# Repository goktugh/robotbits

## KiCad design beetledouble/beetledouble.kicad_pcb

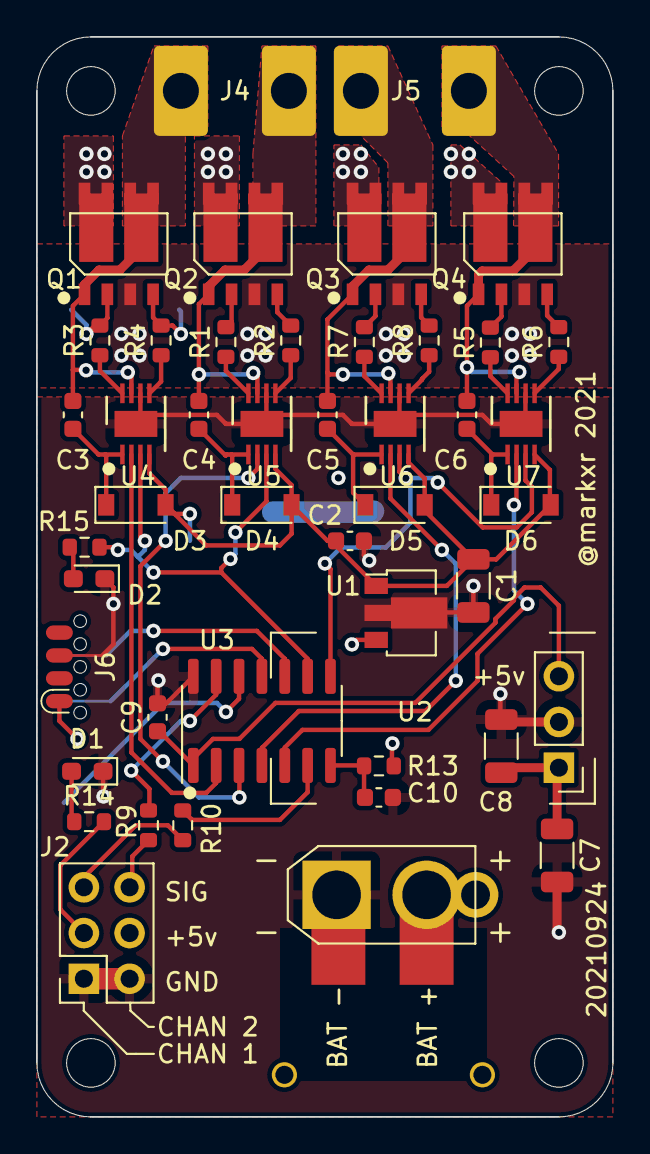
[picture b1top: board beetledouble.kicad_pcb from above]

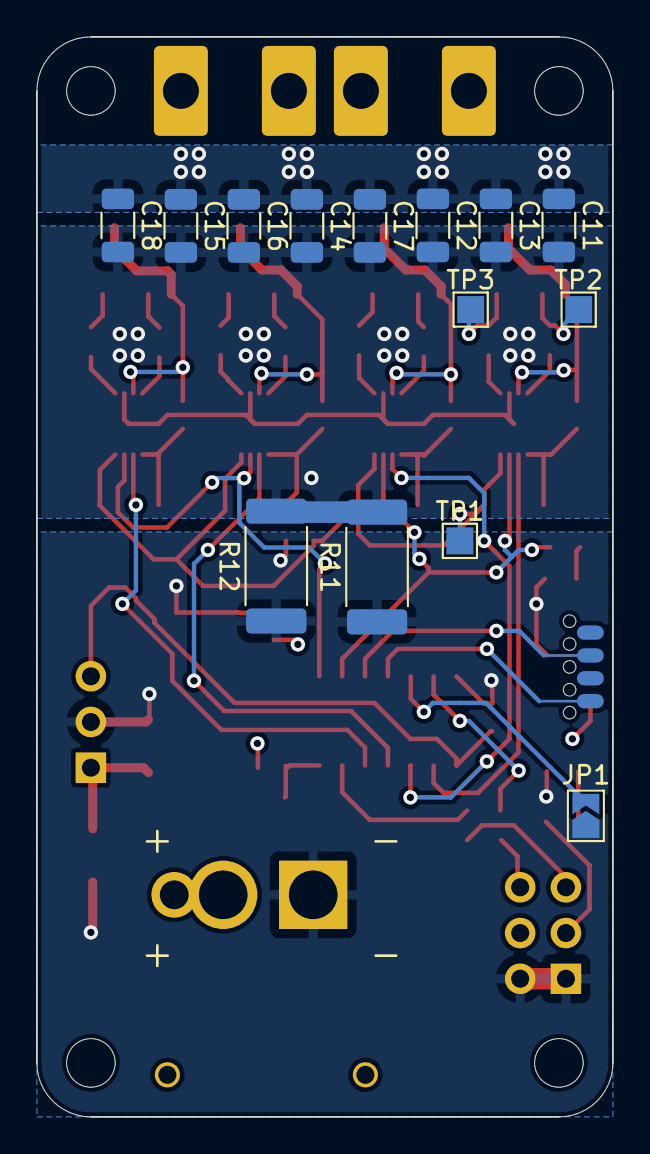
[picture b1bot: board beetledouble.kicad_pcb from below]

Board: 4 copper layers, 32.0 x 60.0 mm, 63 parts (14 on the bottom side), 45 nets.

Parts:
C1, C7, C8, C11, C12, C14, C15: 10uF 50V; C_1206_3216Metric
C2, C3, C4, C5, C6, C10: 2.2uF 50V; C_0603_1608Metric
C9: 0.1uF; C_0603_1608Metric
C13, C16, C17, C18: DNP; C_1206_3216Metric
D1, D2: LED; LED_0603_1608Metric_Pad1.05x0.95mm_HandSolder
D3, D4, D5, D6: B5819W; D_SOD-123
H1, H2, H3, H4: MountingHole; MountingHole_2.7mm_M2.5
J1: XT30PW-M; beetlepower
J2: rxin; PinSocket_2x03_P2.54mm_Vertical
J4, J5: motor_out; beetlemotor
J6: prog connector; SOIC_clipProgSmall
JP1: CONFIG1; SolderJumper-2_P1.3mm_Open_TrianglePad1.0x1.5mm
Q1, Q2, Q3, Q4: SE3082G; Infineon-PG-TDSON
R1, R2, R3, R4, R5, R6, R7, R8: 10R; R_0603_1608Metric
R9, R10, R13, R14, R15: 1k; R_0603_1608Metric
R11, R12: 0.01 ohm; R_2512_6332Metric_Pad1.40x3.35mm_HandSolder
TP1, TP2, TP3: TestPoint; TestPoint_Pad_1.5x1.5mm
U1: 78L12G-AB3-R; SOT-89-3
U2: DD4012SB; aliexpress_regulator_3p
U3: ATtiny1614-SS; SOIC-14_3.9x8.7mm_P1.27mm
U4, U5, U6, U7: NCP81155MN; DFN-8-3x3mm_hand1

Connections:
+5V: C9.1, J2.3, J2.4, R14.2, U2.3 (VOUT), U3.1 (VCC)
+12V: C1.1, C2.1, D3.2 (A), D4.2 (A), D5.2 (A), D6.2 (A), TP1.1, U1.1 (OUT), U4.4 (VCC), U5.4 (VCC), U6.4 (VCC), U7.4 (VCC)
/ISENSE: C10.1, R13.2, U3.7 (PB2)
/P1: J2.5, R10.1
/P2: J2.6, R9.1
/driver1/BOOST1: C3.1, D3.1 (K), U4.1 (BST)
/driver1/BOOST2: C4.1, D4.1 (K), U5.1 (BST)
/driver1/GATEH1: Q1.2 (G), R3.2, TP2.1
/driver1/GATEH2: Q2.2 (G), R1.2
/driver1/GATEL1: Q1.4 (G), R4.2, TP3.1
/driver1/GATEL2: Q2.4 (G), R2.2
/driver1/MOTORH1: R3.1, U4.8 (DRVH)
/driver1/MOTORH2: R1.1, U5.8 (DRVH)
/driver1/MOTORL1: R4.1, U4.5 (DRVL)
/driver1/MOTORL2: R2.1, U5.5 (DRVL)
/driver1/MOTORS1: C3.2, J4.1, Q1.1 (S), Q1.5 (D), Q1.6 (G), U4.7 (SW)
/driver1/MOTORS2: C4.2, J4.2, Q2.1 (S), Q2.5 (D), Q2.6 (G), U5.7 (SW)
/driver2/BOOST1: C5.1, D5.1 (K), U6.1 (BST)
/driver2/BOOST2: C6.1, D6.1 (K), U7.1 (BST)
/driver2/GATEH1: Q3.2 (G), R7.2
/driver2/GATEH2: Q4.2 (G), R5.2
/driver2/GATEL1: Q3.4 (G), R8.2
/driver2/GATEL2: Q4.4 (G), R6.2
/driver2/MOTORH1: R7.1, U6.8 (DRVH)
/driver2/MOTORH2: R5.1, U7.8 (DRVH)
/driver2/MOTORL1: R8.1, U6.5 (DRVL)
/driver2/MOTORL2: R6.1, U7.5 (DRVL)
/driver2/MOTORS1: C5.2, J5.1, Q3.1 (S), Q3.5 (D), Q3.6 (G), U6.7 (SW)
/driver2/MOTORS2: C6.2, J5.2, Q4.1 (S), Q4.5 (D), Q4.6 (G), U7.7 (SW)
CONFIG1: JP1.2 (B), U3.12 (PA2)
GND: C1.2, C2.2, C7.2, C8.2, C9.2, C10.2, D1.1 (K), D2.1 (K), J1.1, J2.1, J2.2, J6.3, JP1.1 (A), R11.1, R12.1, U1.2 (GND), U2.2 (GND), U3.14 (GND), U4.6 (GND), U4.9 (FLAG), U5.6 (GND), U5.9 (FLAG), U6.6 (GND), U6.9 (FLAG), U7.6 (GND), U7.9 (FLAG)
GNDSHUNT: C11.2, C12.2, C13.2, C14.2, C15.2, C16.2, C17.2, C18.2, Q1.3 (S), Q2.3 (S), Q3.3 (S), Q4.3 (S), R11.2, R12.2, R13.1
MOTORF_1: U3.2 (PA4), U4.2 (PWM)
MOTORF_2: U3.4 (PA6), U6.2 (PWM)
MOTORR_1: U3.3 (PA5), U5.2 (PWM)
MOTORR_2: U3.5 (PA7), U7.2 (PWM)
MOTOR_ENABLE_1: R15.2, U3.9 (PB0), U4.3 (EN), U5.3 (EN)
MOTOR_ENABLE_2: U3.8 (PB1), U6.3 (EN), U7.3 (EN)
unnamed: D1.2 (A), R14.1
unnamed: D2.2 (A), R15.1
PWMIN_1: R10.2, U3.6 (PB3)
PWMIN_2: R9.2, U3.13 (PA3)
TXDEBUG: J6.8, U3.11 (PA1)
UPDI: J6.6, U3.10 (~RESET/PA0)
VBAT: C7.1, C8.1, C11.1, C12.1, C13.1, C14.1, C15.1, C16.1, C17.1, C18.1, J1.2, J6.1, Q1.7 (D), Q1.8 (G), Q2.7 (D), Q2.8 (G), Q3.7 (D), Q3.8 (G), Q4.7 (D), Q4.8 (G), U1.3 (IN), U2.1 (VIN)

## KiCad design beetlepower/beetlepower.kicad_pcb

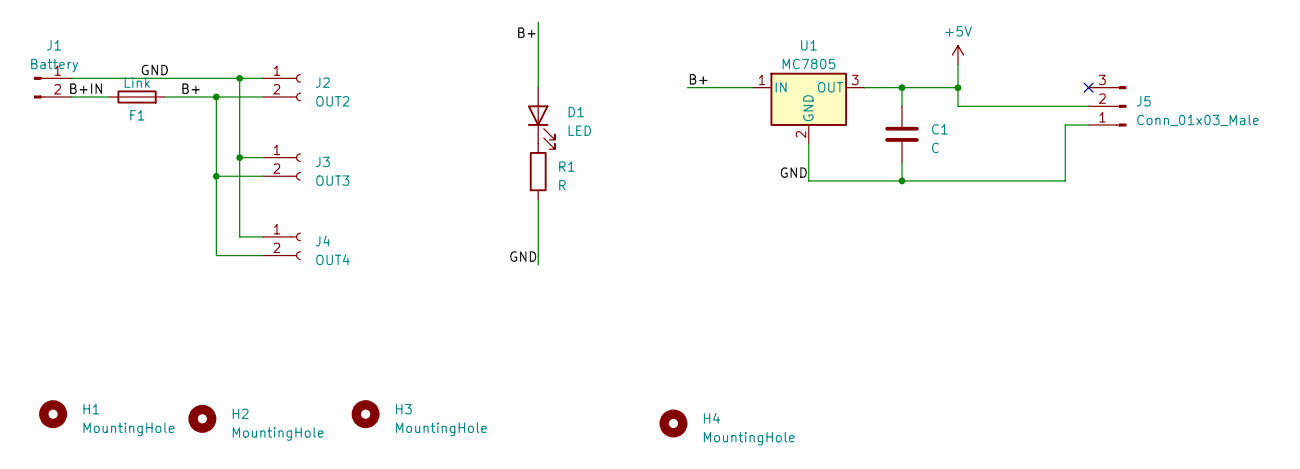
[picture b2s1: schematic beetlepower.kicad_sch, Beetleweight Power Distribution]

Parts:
C1: C; C-pth-and-smd
D1: LED; LED_D5.0mm
F1: Link; XT30U-M
H1, H2, H3, H4: MountingHole; MountingHole_3.2mm_M3
J1: Battery; XT30U-M
J2: OUT2; XT30U-F
J3: OUT3; XT30U-F
J4: OUT4; XT30U-F
J5: Conn_01x03_Male; PinHeader_1x03_P2.54mm_Vertical
R1: R; Resistor-pth-and-smd
U1: MC7805; TO-252-3_TabPin2

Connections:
+5V: C1.1, J5.2, U1.3 (OUT)
/B+: D1.2 (A), F1.2, J2.2, J3.2, J4.2, U1.1 (IN)
/B+IN: F1.1, J1.2
/GND: C1.2, J1.1, J2.1, J3.1, J4.1, J5.1, R1.2, U1.2 (GND)
unnamed: D1.1 (K), R1.1

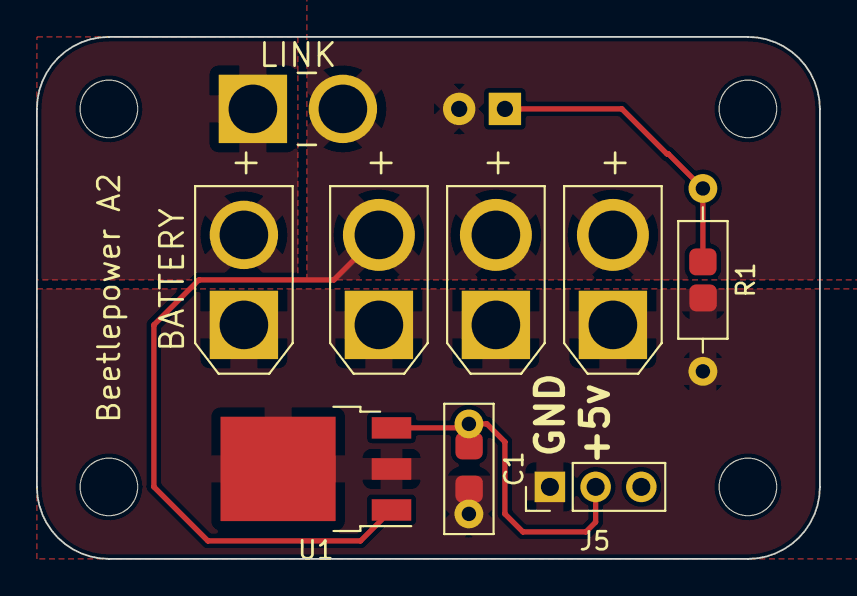
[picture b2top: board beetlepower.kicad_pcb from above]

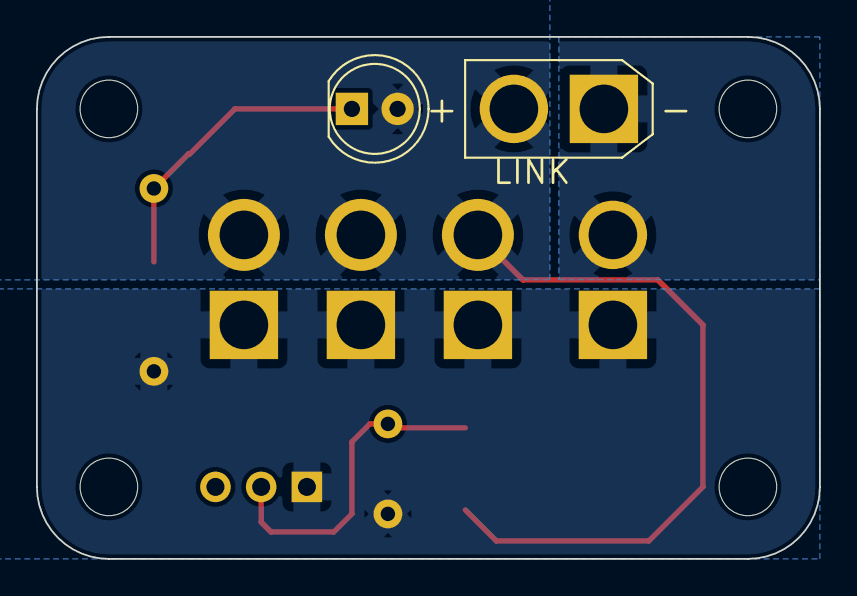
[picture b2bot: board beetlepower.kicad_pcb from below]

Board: 2 copper layers, 43.5 x 29.0 mm, 14 parts (2 on the bottom side), 5 nets.

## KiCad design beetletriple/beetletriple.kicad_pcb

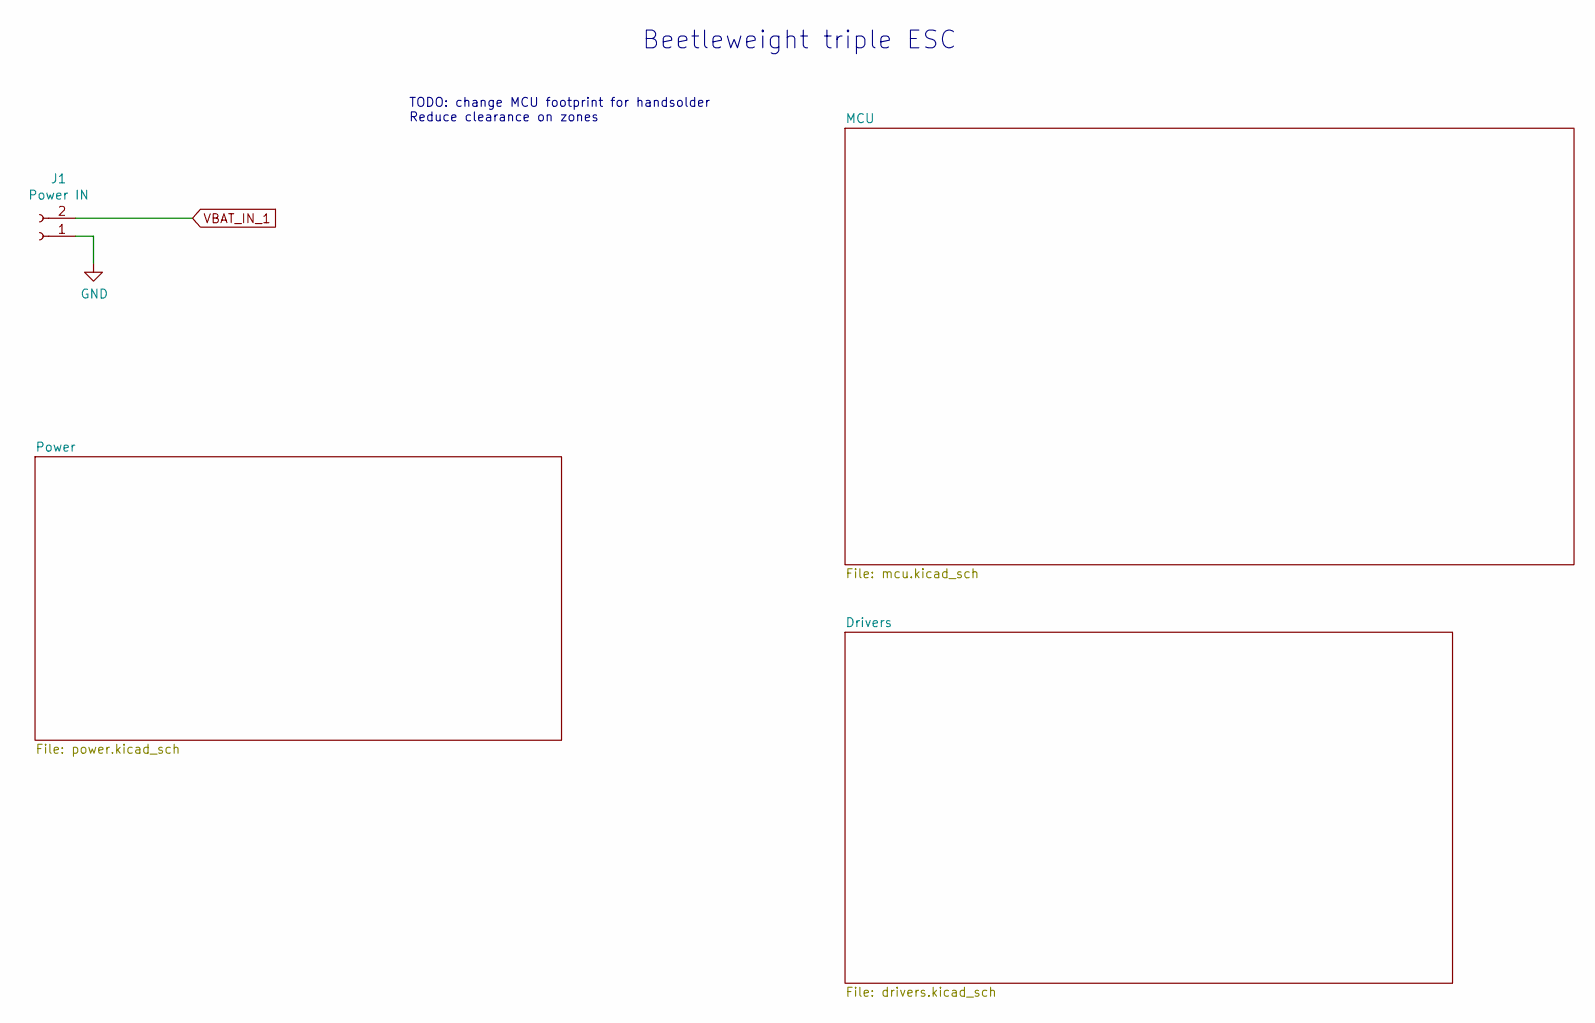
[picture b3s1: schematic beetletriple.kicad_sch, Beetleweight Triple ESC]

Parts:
J1: Power IN; beetlepower

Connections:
GND: J1.1; also elsewhere on the board
VBAT_IN_1: J1.2; also elsewhere on the board

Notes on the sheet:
TODO: change MCU footprint for handsolder Reduce clearance on zones
Beetleweight triple ESC

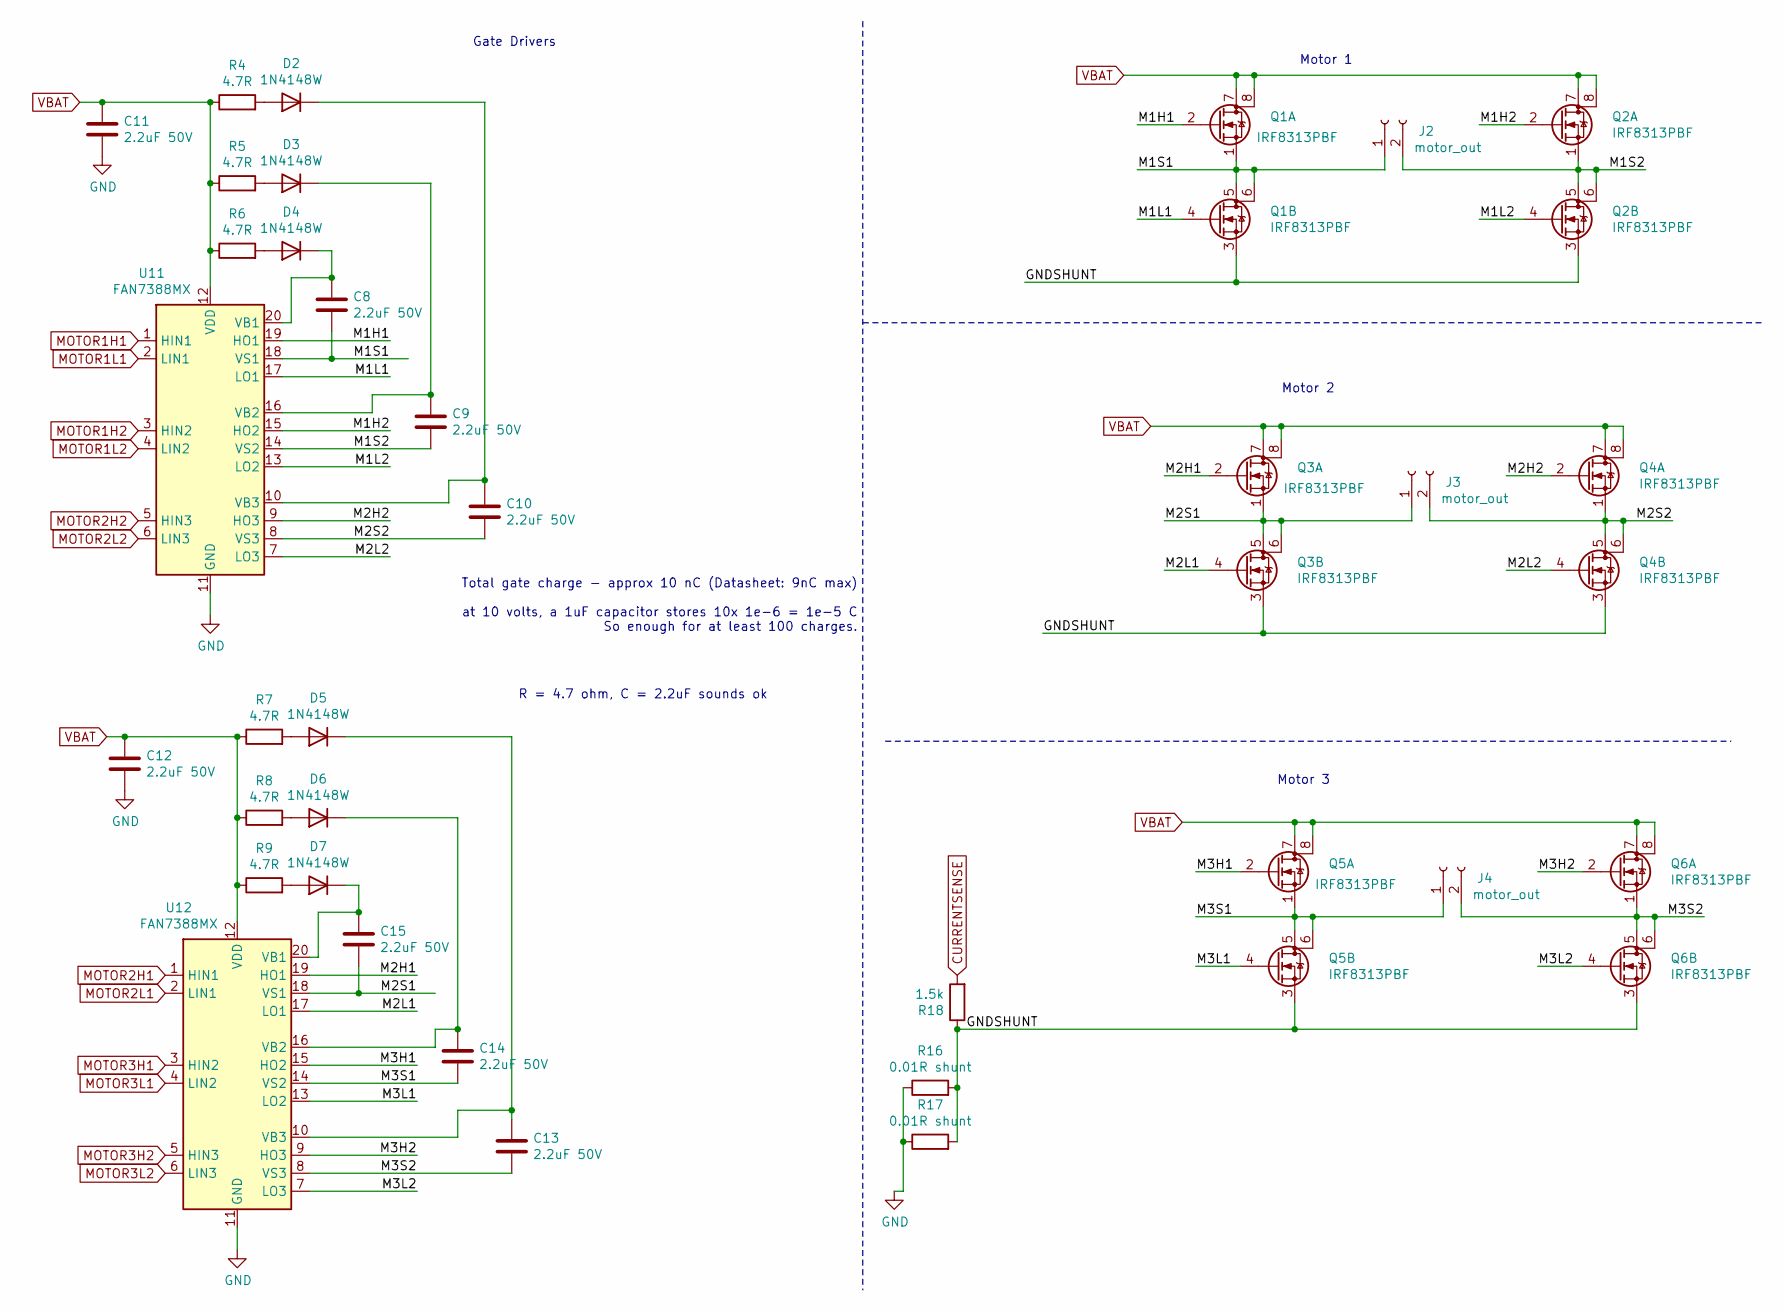
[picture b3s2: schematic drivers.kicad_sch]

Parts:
C8, C9, C10, C11, C12, C13, C14, C15: 2.2uF 50V; C_1206_3216Metric; LCSC C50254
D2, D3, D4, D5, D6, D7: 1N4148W; D_SOD-123; MPN 1N4148W; LCSC C81598
J2, J3, J4: motor_out; TerminalBlock_motor
Q1, Q2, Q3, Q4, Q5, Q6: IRF8313PBF; SOIC-8_3.9x4.9mm_P1.27mm; LCSC C57696
R4, R5, R6, R7, R8, R9: 4.7R; R_0805_2012Metric; LCSC C17675
R16, R17: 0.01R shunt; R_2512_6332Metric_Pad1.40x3.35mm_HandSolder
R18: 1.5k; R_0805_2012Metric; LCSC C4310
U11, U12: FAN7388MX; SOIC-20W_7.5x12.8mm_P1.27mm; LCSC C124451

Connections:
/Drivers/GNDSHUNT: Q1.3 (S), Q2.3 (S), Q3.3 (S), Q4.3 (S), Q5.3 (S), Q6.3 (S), R16.2, R17.2, R18.1
/Drivers/M1H1: Q1.2 (G), U11.19 (HO1)
/Drivers/M1H2: Q2.2 (G), U11.15 (HO2)
/Drivers/M1L1: Q1.4 (G), U11.17 (LO1)
/Drivers/M1L2: Q2.4 (G), U11.13 (LO2)
/Drivers/M1S1: C8.2, J2.1, Q1.1 (S), Q1.5 (D), Q1.6 (D), U11.18 (VS1)
/Drivers/M1S2: C9.2, J2.2, Q2.1 (S), Q2.5 (D), Q2.6 (D), U11.14 (VS2)
/Drivers/M2H1: Q3.2 (G), U12.19 (HO1)
/Drivers/M2H2: Q4.2 (G), U11.9 (HO3)
/Drivers/M2L1: Q3.4 (G), U12.17 (LO1)
/Drivers/M2L2: Q4.4 (G), U11.7 (LO3)
/Drivers/M2S1: C15.2, J3.1, Q3.1 (S), Q3.5 (D), Q3.6 (D), U12.18 (VS1)
/Drivers/M2S2: C10.2, J3.2, Q4.1 (S), Q4.5 (D), Q4.6 (D), U11.8 (VS3)
/Drivers/M3H1: Q5.2 (G), U12.15 (HO2)
/Drivers/M3H2: Q6.2 (G), U12.9 (HO3)
/Drivers/M3L1: Q5.4 (G), U12.13 (LO2)
/Drivers/M3L2: Q6.4 (G), U12.7 (LO3)
/Drivers/M3S1: C14.2, J4.1, Q5.1 (S), Q5.5 (D), Q5.6 (D), U12.14 (VS2)
/Drivers/M3S2: C13.2, J4.2, Q6.1 (S), Q6.5 (D), Q6.6 (D), U12.8 (VS3)
CURRENTSENSE: R18.2; also elsewhere on the board
GND: C11.2, C12.2, R16.1, R17.1, U11.11 (GND), U12.11 (GND); also elsewhere on the board
MOTOR1H1: U11.1 (HIN1); also elsewhere on the board
MOTOR1H2: U11.3 (HIN2); also elsewhere on the board
MOTOR1L1: U11.2 (LIN1); also elsewhere on the board
MOTOR1L2: U11.4 (LIN2); also elsewhere on the board
MOTOR2H1: U12.1 (HIN1); also elsewhere on the board
MOTOR2H2: U11.5 (HIN3); also elsewhere on the board
MOTOR2L1: U12.2 (LIN1); also elsewhere on the board
MOTOR2L2: U11.6 (LIN3); also elsewhere on the board
MOTOR3H1: U12.3 (HIN2); also elsewhere on the board
MOTOR3H2: U12.5 (HIN3); also elsewhere on the board
MOTOR3L1: U12.4 (LIN2); also elsewhere on the board
MOTOR3L2: U12.6 (LIN3); also elsewhere on the board
unnamed: C8.1, D4.1 (K), U11.20 (VB1)
unnamed: C9.1, D3.1 (K), U11.16 (VB2)
unnamed: C10.1, D2.1 (K), U11.10 (VB3)
unnamed: C13.1, D5.1 (K), U12.10 (VB3)
unnamed: C14.1, D6.1 (K), U12.16 (VB2)
unnamed: C15.1, D7.1 (K), U12.20 (VB1)
unnamed: D2.2 (A), R4.2
unnamed: D3.2 (A), R5.2
unnamed: D4.2 (A), R6.2
unnamed: D5.2 (A), R7.2
unnamed: D6.2 (A), R8.2
unnamed: D7.2 (A), R9.2
VBAT: C11.1, C12.1, Q1.7 (D), Q1.8 (D), Q2.7 (D), Q2.8 (D), Q3.7 (D), Q3.8 (D), Q4.7 (D), Q4.8 (D), Q5.7 (D), Q5.8 (D), Q6.7 (D), Q6.8 (D), R4.1, R5.1, R6.1, R7.1, R8.1, R9.1, U11.12 (VDD), U12.12 (VDD); also elsewhere on the board

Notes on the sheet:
Gate Drivers
R = 4.7 ohm, C = 2.2uF sounds ok
Total gate charge - approx 10 nC (Datasheet: 9nC max) at 10 volts, a 1uF capacitor stores 10x 1e-6 = 1e-5 C So enough for at least 100 charges.
Motor 3
Motor 2
Motor 1

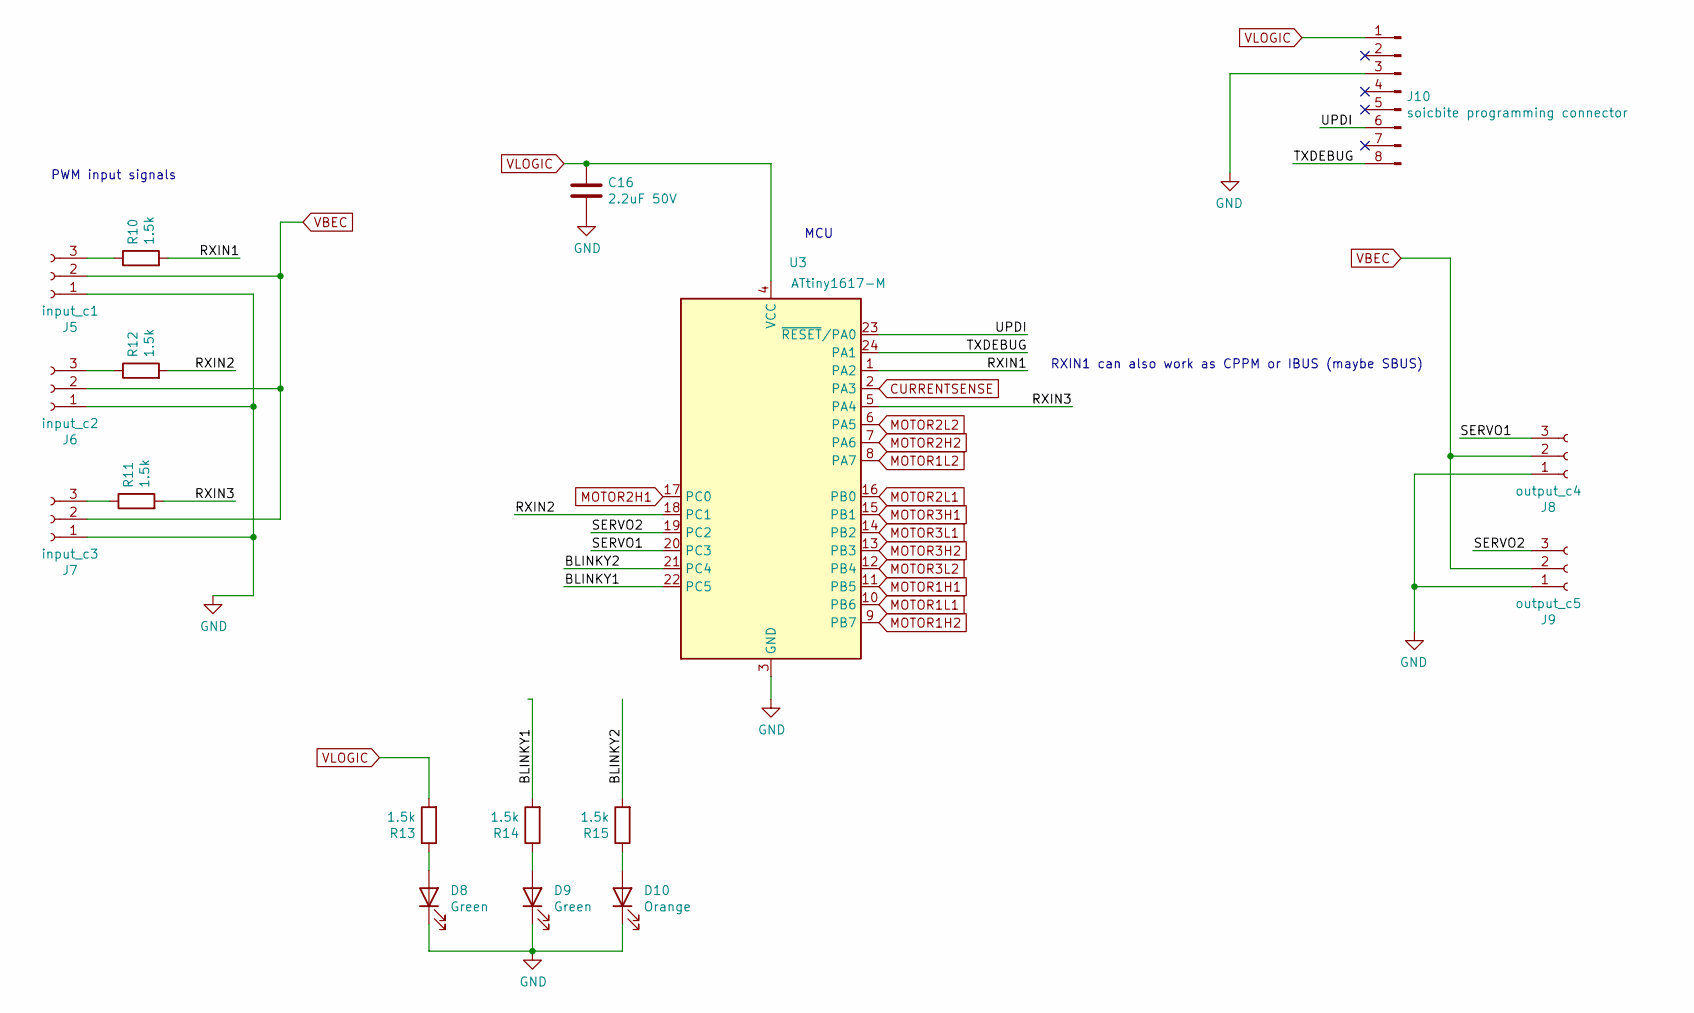
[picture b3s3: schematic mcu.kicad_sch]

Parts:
C16: 2.2uF 50V; C_1206_3216Metric; LCSC C50254
D8, D9: Green; LED_0805_2012Metric; LCSC C2297
D10: Orange; LED_0805_2012Metric; LCSC C84262
J5: input_c1; PinHeader_1x03_P2.54mm_Vertical
J6: input_c2; PinHeader_1x03_P2.54mm_Vertical
J7: input_c3; PinHeader_1x03_P2.54mm_Vertical
J8: output_c4; PinHeader_1x03_P2.54mm_Vertical
J9: output_c5; PinHeader_1x03_P2.54mm_Vertical
J10: soicbite programming connector; SOIC_clipProgSmall
R10, R11, R12, R13, R14, R15: 1.5k; R_0805_2012Metric; LCSC C4310
U3: ATtiny1617-M; QFN-24-1EP_4x4mm_P0.5mm_EP2.6x2.6mm; LCSC C194193

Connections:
/MCU/BLINKY1: R14.2, U3.22 (PC5)
/MCU/BLINKY2: R15.2, U3.21 (PC4)
/MCU/RXIN1: R10.2, U3.1 (PA2)
/MCU/RXIN2: R12.2, U3.18 (PC1)
/MCU/RXIN3: R11.2, U3.5 (PA4)
/MCU/SERVO1: J8.3, U3.20 (PC3)
/MCU/SERVO2: J9.3, U3.19 (PC2)
/MCU/TXDEBUG: J10.8, U3.24 (PA1)
/MCU/UPDI: J10.6, U3.23 (~RESET~/PA0)
CURRENTSENSE: U3.2 (PA3); also elsewhere on the board
GND: C16.2, D8.1 (K), D9.1 (K), D10.1 (K), J5.1, J6.1, J7.1, J8.1, J9.1, J10.3, U3.3 (GND), U3.25 (GND); also elsewhere on the board
MOTOR1H1: U3.11 (PB5); also elsewhere on the board
MOTOR1H2: U3.9 (PB7); also elsewhere on the board
MOTOR1L1: U3.10 (PB6); also elsewhere on the board
MOTOR1L2: U3.8 (PA7); also elsewhere on the board
MOTOR2H1: U3.17 (PC0); also elsewhere on the board
MOTOR2H2: U3.7 (PA6); also elsewhere on the board
MOTOR2L1: U3.16 (PB0); also elsewhere on the board
MOTOR2L2: U3.6 (PA5); also elsewhere on the board
MOTOR3H1: U3.15 (PB1); also elsewhere on the board
MOTOR3H2: U3.13 (PB3); also elsewhere on the board
MOTOR3L1: U3.14 (PB2); also elsewhere on the board
MOTOR3L2: U3.12 (PB4); also elsewhere on the board
unnamed: D8.2 (A), R13.1
unnamed: D9.2 (A), R14.1
unnamed: D10.2 (A), R15.1
unnamed: J5.3, R10.1
unnamed: J6.3, R12.1
unnamed: J7.3, R11.1
VBEC: J5.2, J6.2, J7.2, J8.2, J9.2; also elsewhere on the board
VLOGIC: C16.1, J10.1, R13.2, U3.4 (VCC); also elsewhere on the board

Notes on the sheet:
PWM input signals
MCU
RXIN1 can also work as CPPM or IBUS (maybe SBUS)

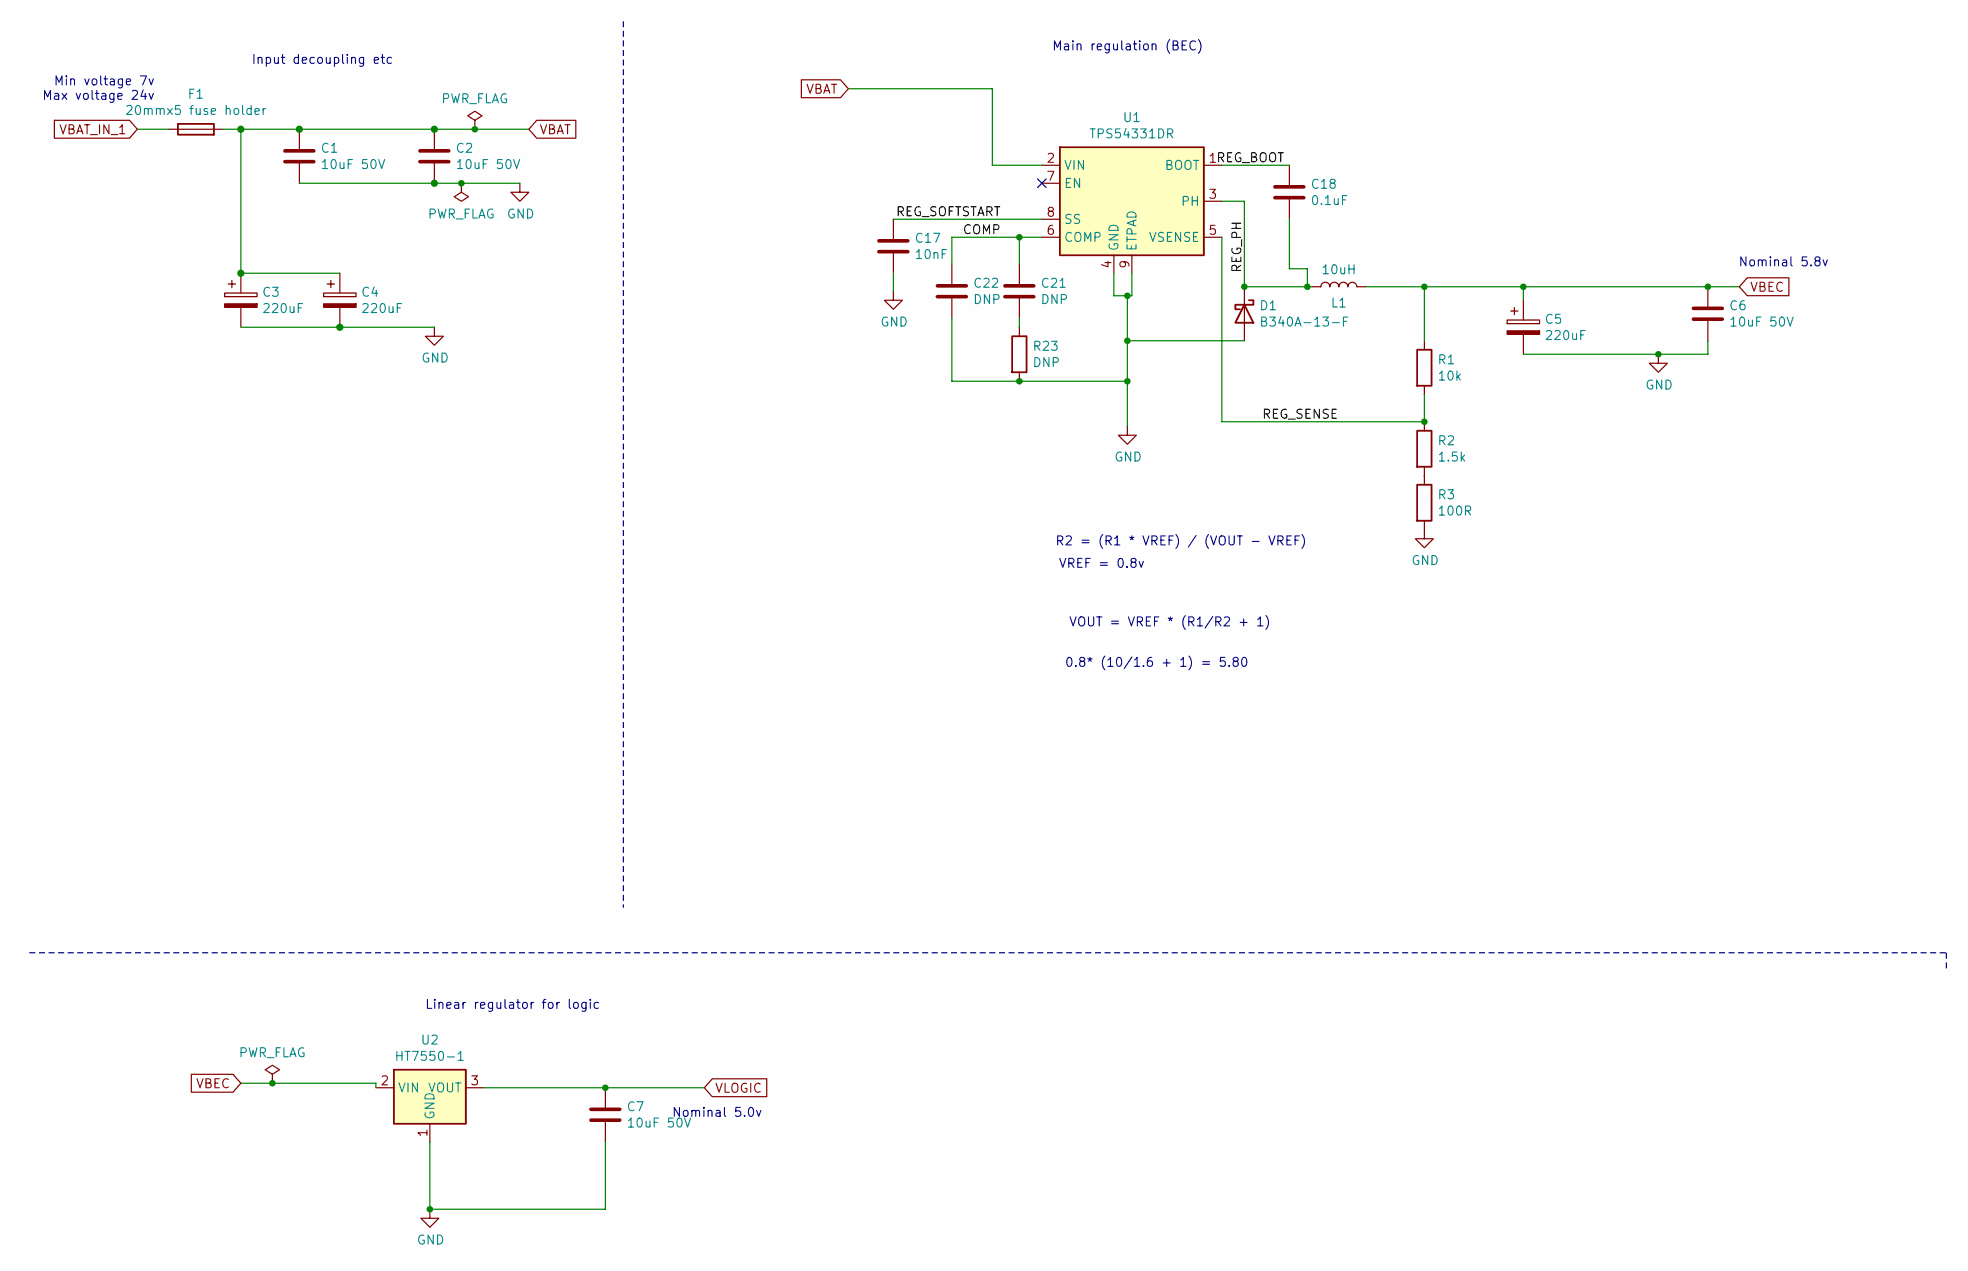
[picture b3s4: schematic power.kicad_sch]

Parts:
C1, C2, C6, C7: 10uF 50V; C_1206_3216Metric; LCSC C13585
C3, C4, C5: 220uF; C_Elec_10x10.2; LCSC C125977
C17: 10nF; C_1206_3216Metric; LCSC C1846
C18: 0.1uF; C_1206_3216Metric; LCSC C24497
C21, C22: DNP; C_1206_3216Metric
D1: B340A-13-F; D_SMA_Handsoldering; MPN B340A; LCSC C85098
F1: 20mmx5 fuse holder; fuseholder_flexible
L1: 10uH; L_12x12mm_H4.5mm; MPN YSPI1040-101M; LCSC C497890
R1: 10k; R_0805_2012Metric; LCSC C17414
R2: 1.5k; R_0805_2012Metric; LCSC C4310
R3: 100R; R_0805_2012Metric; LCSC C17408
R23: DNP; R_0805_2012Metric
U1: TPS54331DR; TI_SO-PowerPAD-8_ThermalVias; LCSC C9865
U2: HT7550-1; SOT-89-3; LCSC C16106

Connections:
/Power/COMP: C21.1, C22.1, U1.6 (COMP)
/Power/REG_BOOT: C18.1, U1.1 (BOOT)
/Power/REG_PH: C18.2, D1.1 (K), L1.1, U1.3 (PH)
/Power/REG_SENSE: R1.2, R2.1, U1.5 (VSENSE)
/Power/REG_SOFTSTART: C17.1, U1.8 (SS)
GND: C1.2, C2.2, C3.2, C4.2, C5.2, C6.2, C7.2, C17.2, C22.2, D1.2 (A), R3.2, R23.2, U1.4 (GND), U1.9 (ETPAD), U2.1 (GND); also elsewhere on the board
unnamed: C21.2, R23.1
unnamed: R2.2, R3.1
VBAT: C1.1, C2.1, C3.1, C4.1, F1.2, U1.2 (VIN); also elsewhere on the board
VBAT_IN_1: F1.1; also elsewhere on the board
VBEC: C5.1, C6.1, L1.2, R1.1, U2.2 (VIN); also elsewhere on the board
VLOGIC: C7.1, U2.3 (VOUT); also elsewhere on the board

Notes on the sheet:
Min voltage 7v Max voltage 24v
Input decoupling etc
Linear regulator for logic
Nominal 5.0v
0.8* (10/1.6 + 1) = 5.80
VREF = 0.8v
Main regulation (BEC)
VOUT = VREF * (R1/R2 + 1)
R2 = (R1 * VREF) / (VOUT - VREF)
Nominal 5.8v

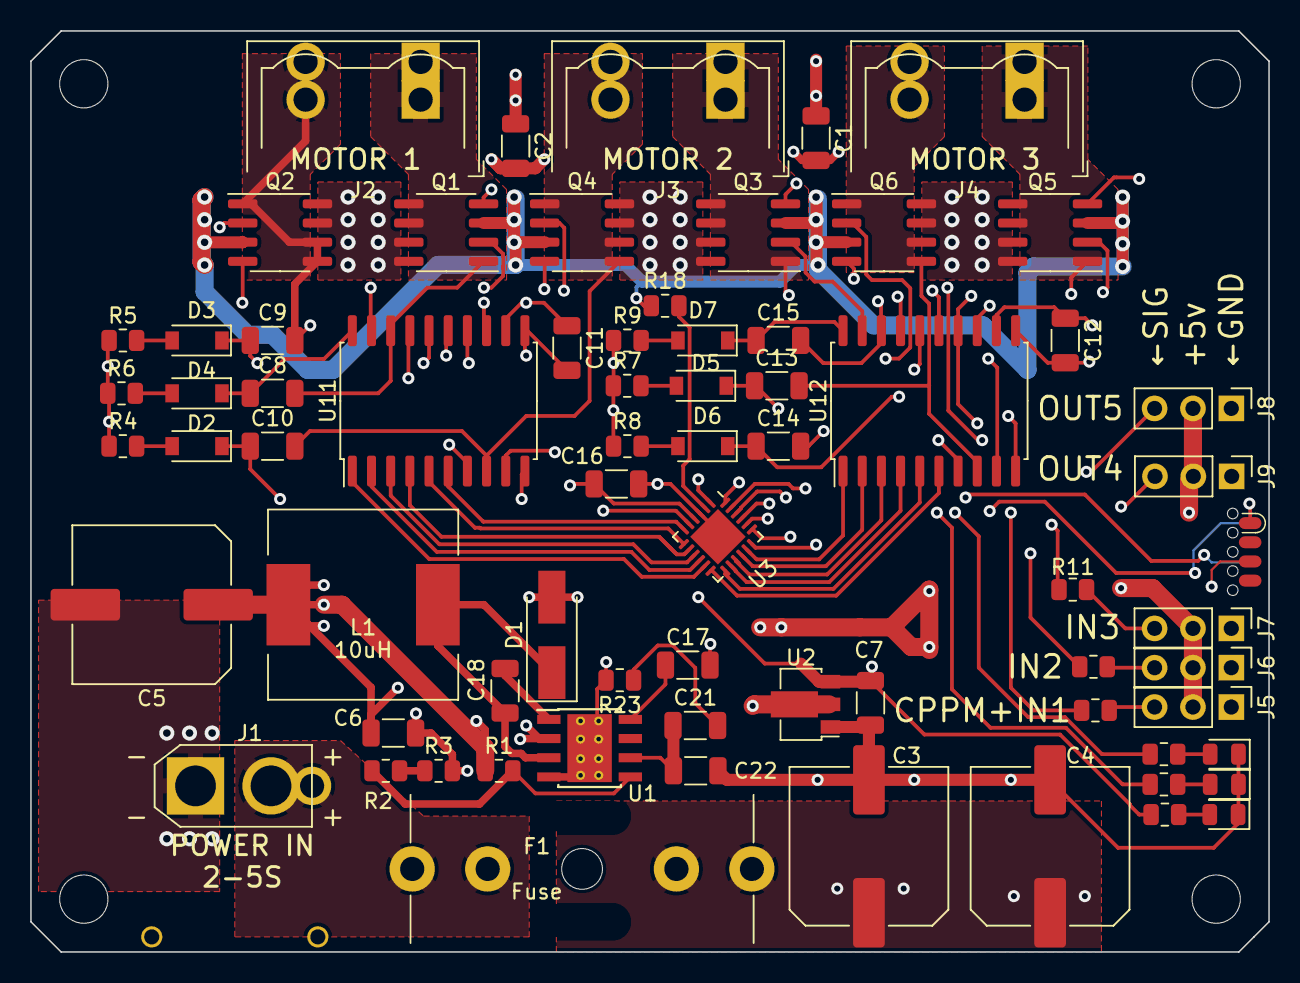
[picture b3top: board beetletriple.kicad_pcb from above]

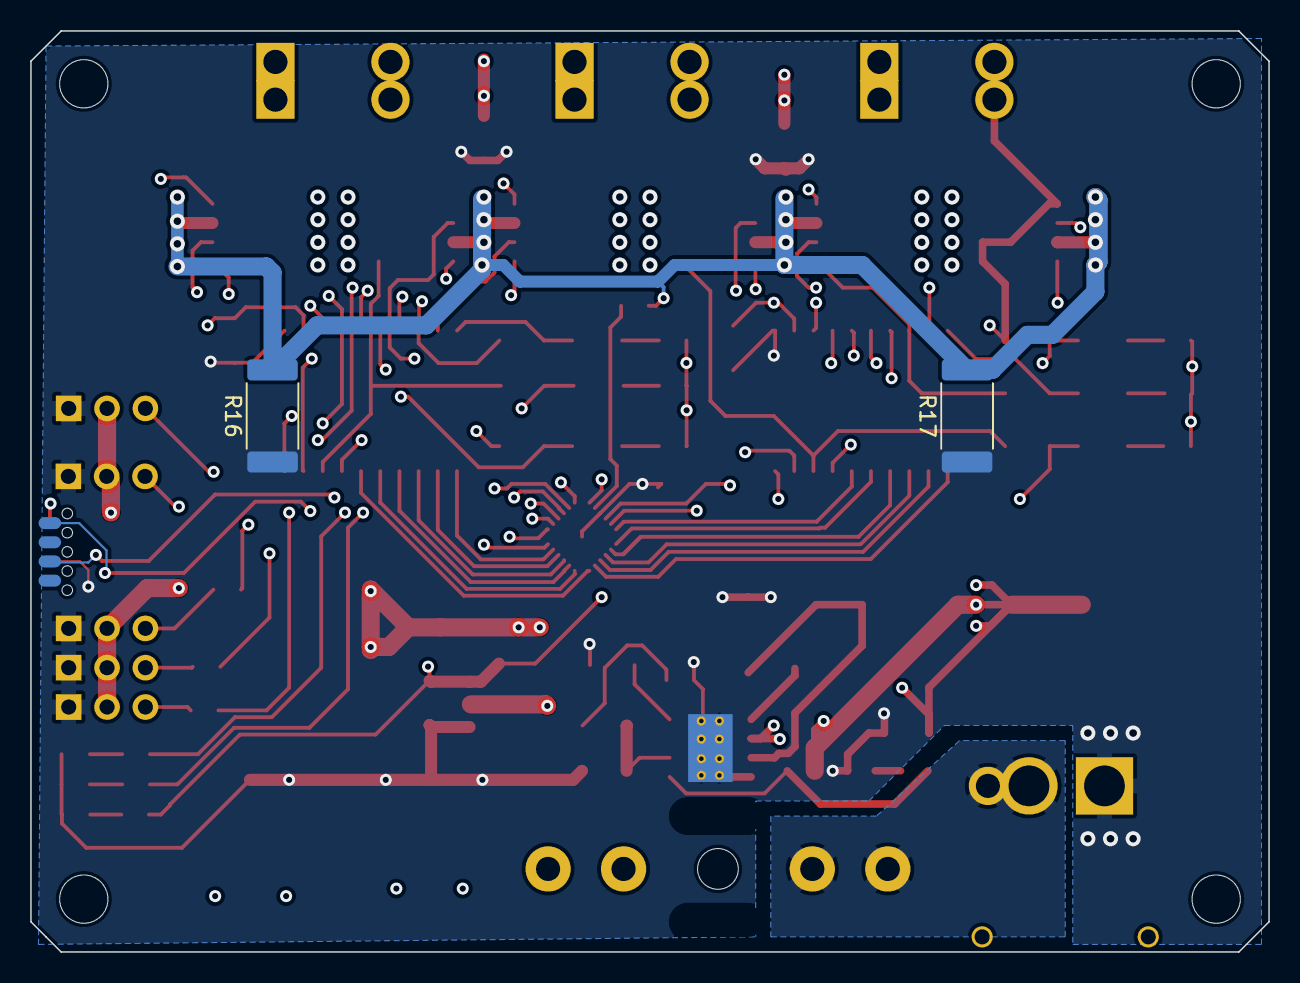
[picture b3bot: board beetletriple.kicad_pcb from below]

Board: 4 copper layers, 82.0 x 61.0 mm, 72 parts (2 on the bottom side), 71 nets.
